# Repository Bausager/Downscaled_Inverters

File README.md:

# Downscaled three-phase half-bridge inverter
This project is an inverter framework for students and researches to learn, test and research state-of-the-art phase-lock-loops and control algorithms.
The inverters manly uses jellybean components, found free at the electronic laboratory for electrical engineers at Aarhus University(AU) for their students.
The purpose is to make an inexpensive and save platform instead of having to work with line voltages. 
This means all the components can be downscaled to work with 5 volt.
Here the inverter can be powered by a USB and supply its own grid.

This is an accumulative project, this means it's going to improve over time. 
There's a limited number of people working on this which means updates somethimes takes sometime.
If you want to help improve, collaborate or have something in your back pocket you want to integrate, you are very welcome to contact me!
The more the merrier!

There're some restrictions!
Since this is an open-source, student use it and research need to be understood and replicated, the code needs to be written in such a way that other prople can understand it.
Even if the person isn't an expert.
That is importent!

New fueatures waiting to be implemented can be found on the github project site [Not a Generator (NaG)](https://github.com/users/Bausager/projects/2)

## University Teaching

### Phase-Lock-Loop(PLL)
Many students at AU before this project have worked in PLLs for their bachelor thesis that meant a large part of the project was making an inverter from scratch.
This allows students not to reinvent the wheel if they are interested in other aspects than the hardware side.
With this the students can generate the grid and test their PLL on the some PCB, which lowest the bar of entre and in turn makes student projects and bachelor thesis more focused.

### Control
The students have the ability to develop control methods and test it only with a one inverter and output impedances.
Here different filter configuration or switching methods can also influence the THD which the students new have a direct way to interacting with.

### Power Factor Correction(PFC)
This PCB also allows to make it work as a PFC where control, THD and other aspects can be looked into.
Here a PFC input with a inverter output can also be pursued.

## Research Projects
Even if grid impedances does not downscale well, control algorithms, stability and many other advanced concept can be tested.
In the future, a new version of the PCB will be made for increasing the DC Link voltage to accommodate some of the downsides of the downscaled grid impedances.
As the time of writing the increase of DC Link voltage would be around 24V.
Now multiply inverters can be chained to a common grid to research stability.
Here the goal is not only to use the same micro-controller and control but to use different kinds of controls, PLLs, micro-controller, changing grid impedances, short-circuits and much more.
This will also include black start, synchronisation and much more.

## Collaborators
This project was initially an idea developed under [Associate Professor Uffe Jakobsen](https://pure.au.dk/portal/en/persons/uja%40ece.au.dk) for his classes and research into inverter control.
He also has students doing their project and bachelor thesis helping expand on this project.

A contributor [Christian Lind Vie Madsen](https://www.linkedin.com/in/christian-karl-oscar-lind-vie-madsen-11606a9b/) helps optimising written code for better performance.

And project maintainer- Me! [Michelle Bausager](https://www.linkedin.com/in/michelle-bausager/) A former student and research assistance at AU who likes to work with all aspects of inverters.

## Git Workflow.
For students or others who want to contribute, a workflow is needed to make sure everything still works in the end.
main.c on the main branch is written in such a way that every function is implementet but commented out.
This means there's a funtional implementation of every feature avaliable ready to use.

To make sure the workflow is allined a smal guide it here presented;

### Download the repository and work on an existing branch
Create of find a folder for the Git project and open your terminal in that folder.
Grab the git link and use the following git commands to download the project
```
git clone https://github.com/Bausager/Downscaled_Inverters.git
```
It’s good practice to get an overview of the project, especially the branches.
It's also here you would start if you come back to code some more!
```
git pull
git branch -a
```
There’s probably a need to code in a specific branch, if you're not in the right branch you need to select it from the list. 
Now you need to update it localy as follows:
```
git checkout specific_branch
git pull origin specific_branch
```
You can now start to make changes to the code!
To commit it, firstly you need to make sure the branch is up to date.
Then the "git add -A" commits all files and now you have to write some comments on the changes you made
Now you can push it to git!
```
git pull origin specific_branch
git add -A
git commit -m "Head line for changes
>
>
> Discription of what has been done "
git push origin specific_branch
```

### Make a new branch
Firstly make sure you have been invited to be a contributor.
Then starting working on a new feature first pull from the main branch
```
git pull origin main
```
Now you need to create a new branch where you can make your new implementations. Remember to give it a valuable name, such as "UltraCoolNewPLL".
After creating it you need to be in ýour new branch, with the opteration "checkout".
```
git branch new_branch
git checkout new_branch
```
You can now start to make changes to the code!
Since it's a new branch you don't need to make sure it's already updated as you do after you've commitet the branch for the first time.
Then the "git add -A" commits all files and now you have to write some comments on the changes you made.
```
git add -A
git commit -m "Head line for changes
>
>
> Discription of what has been done "
```
First time pushing a new branch you need to push it like this
```
git push -u origin new_branch
```
After that you can simply go to the workflow presented in *Download the repository and work on an existing branch*

### Marge branch to main
When the feature is done and tested, it's time to merge with the main branch.
This is the time and place where everything can go wrong!
Make sure main.c is steamlined like seen in the current main.c.
We're trying to implement every feature just outcommedted, that means you can just outcomment the feature to make it work.
At least that is what we're trying to do, to have a good example for the implementation for others to look at.
When we merge we need to be on the main branch.
```
git checkout main
git pull origin main
```
Now we can merge the branch into the main branch.
```
git merge new_branch
git push origin main
```
Now we’re ready to delete our branch. First we see what branches are merged, just to make sure we’re
deleting the right one. Then we delete the local branch and then the remote branch we associated with the
remote repository.
```
git branch --merged
git branch -d new_branch
git push origin --delete new_branch
```
And now it's done.

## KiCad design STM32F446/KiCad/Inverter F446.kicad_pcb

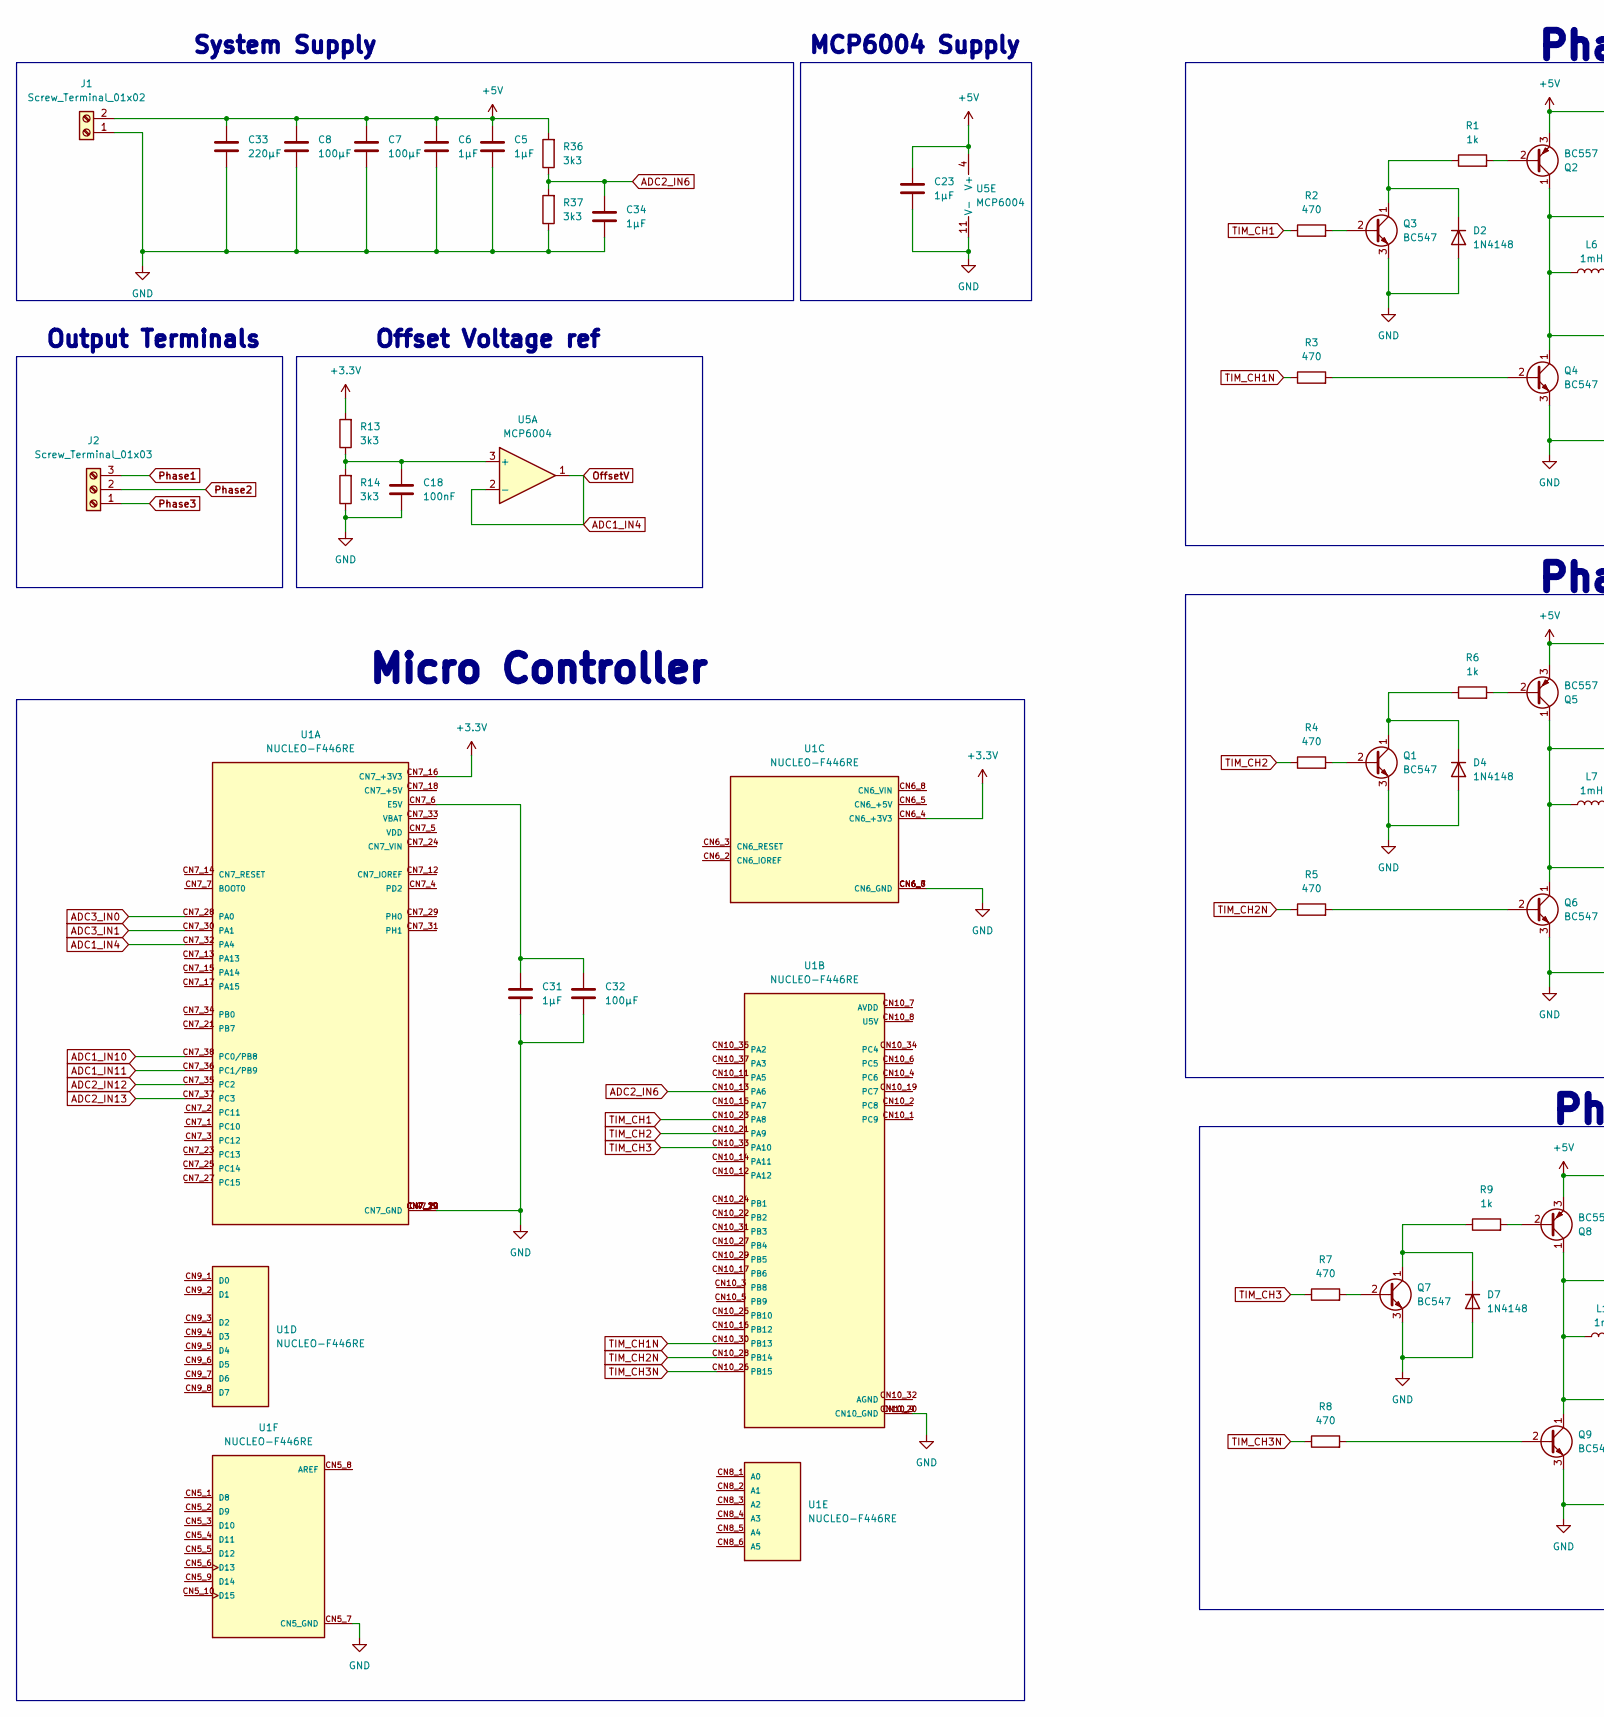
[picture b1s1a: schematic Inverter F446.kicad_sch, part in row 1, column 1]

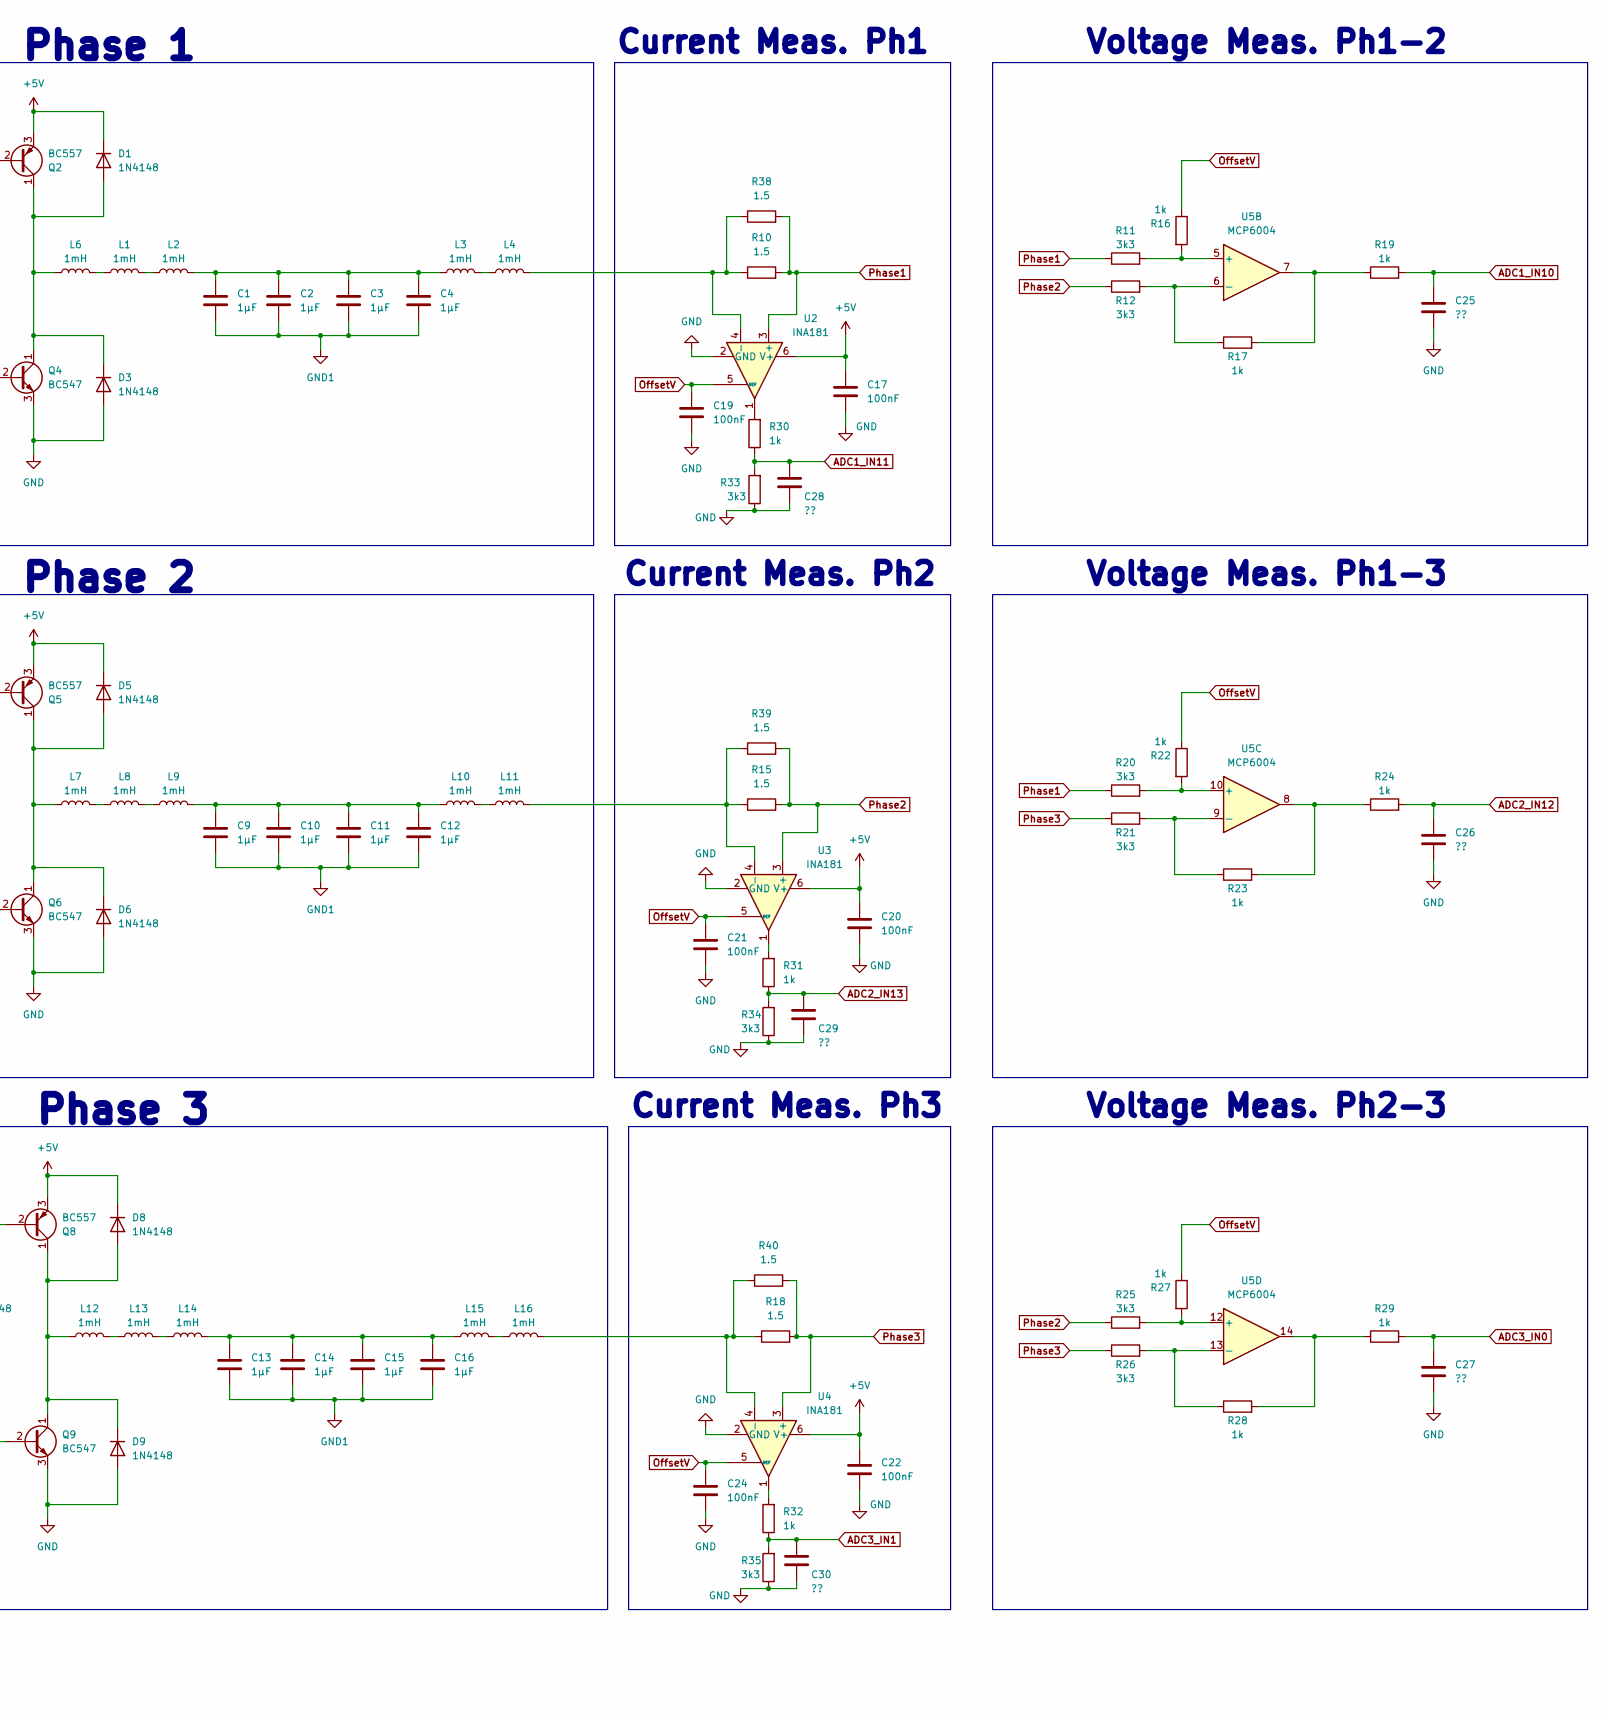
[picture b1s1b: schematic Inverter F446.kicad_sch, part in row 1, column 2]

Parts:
C1, C2, C3, C4, C5, C6, C9, C10, C11, C12, C13, C14, C15, C16, C23, C31, C34: 1µF; C_Disc_D7.5mm_W5.0mm_P5.00mm
C7, C8, C32: 100µF; CP_Radial_D6.3mm_P2.50mm
C17, C18, C19, C20, C21, C22, C24: 100nF; C_Disc_D7.5mm_W2.5mm_P5.00mm
C25, C26, C27, C28, C29, C30: ??; C_Disc_D7.5mm_W5.0mm_P5.00mm
C33: 220µF; CP_Radial_D8.0mm_P5.00mm
D1, D2, D3, D4, D5, D6, D7, D8, D9: 1N4148; D_DO-35_SOD27_P7.62mm_Horizontal
J1: Screw_Terminal_01x02; TerminalBlock_bornier-2_P5.08mm
J2: Screw_Terminal_01x03; TerminalBlock_bornier-3_P5.08mm
L1, L2, L3, L4, L6, L7, L8, L9, L10, L11, L12, L13, L14, L15, L16: 1mH; L_Axial_L12.0mm_D5.0mm_P15.24mm_Horizontal_Fastron_MISC
Q1, Q3, Q4, Q6, Q7, Q9: BC547; TO-92_Inline
Q2, Q5, Q8: BC557; TO-92_Inline
R1, R6, R9, R16, R17, R19, R22, R23, R24, R27, R28, R29, R30, R31, R32: 1k; R_Axial_DIN0207_L6.3mm_D2.5mm_P10.16mm_Horizontal
R2, R3, R4, R5, R7, R8: 470; R_Axial_DIN0207_L6.3mm_D2.5mm_P10.16mm_Horizontal
R10, R15, R18, R38, R39, R40: 1.5; R_Axial_DIN0207_L6.3mm_D2.5mm_P10.16mm_Horizontal
R11, R12, R13, R14, R20, R21, R25, R26, R33, R34, R35, R36, R37: 3k3; R_Axial_DIN0207_L6.3mm_D2.5mm_P10.16mm_Horizontal
U1: NUCLEO-F446RE; MODULE_NUCLEO-F446RE; PARTREV 13
U2, U3, U4: INA181; SOT-23-6
U5: MCP6004; DIP-14_W7.62mm_Socket

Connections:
+3.3V: R13.2, U1.CN6_4 (CN6_+3V3), U1.CN7_16 (CN7_+3V3)
+5V: C5.1, C6.1, C7.1, C8.1, C17.1, C20.1, C22.1, C23.1, C33.1, D1.1 (K), D5.1 (K), D8.1 (K), J1.2, Q2.3 (E), Q5.3 (E), Q8.3 (E), R36.2, U2.6 (V+), U3.6 (V+), U4.6 (V+), U5.4 (V+)
ADC1_IN4: C19.1, C21.1, C24.1, R16.1, R22.1, R27.1, U1.CN7_32 (PA4), U2.5 (REF), U3.5 (REF), U4.5 (REF), U5.1, U5.2 (-)
ADC1_IN10: C25.1, R19.2, U1.CN7_38 (PC0/PB8)
ADC1_IN11: C28.1, R30.1, R33.2, U1.CN7_36 (PC1/PB9)
ADC2_IN6: C34.1, R36.1, R37.2, U1.CN10_13 (PA6)
ADC2_IN12: C26.1, R24.2, U1.CN7_35 (PC2)
ADC2_IN13: C29.1, R31.1, R34.2, U1.CN7_37 (PC3)
ADC3_IN0: C27.1, R29.2, U1.CN7_28 (PA0)
ADC3_IN1: C30.1, R32.1, R35.2, U1.CN7_30 (PA1)
GND: C5.2, C6.2, C7.2, C8.2, C17.2, C18.2, C19.2, C20.2, C21.2, C22.2, C23.2, C24.2, C25.2, C26.2, C27.2, C28.2, C29.2, C30.2, C31.2, C32.2, C33.2, C34.2, D2.2 (A), D3.2 (A), D4.2 (A), D6.2 (A), D7.2 (A), D9.2 (A), J1.1, Q1.3 (E), Q3.3 (E), Q4.3 (E), Q6.3 (E), Q7.3 (E), Q9.3 (E), R14.1, R33.1, R34.1, R35.1, R37.1, U1.CN5_7 (CN5_GND), U1.CN6_6 (CN6_GND), U1.CN6_7 (CN6_GND), U1.CN7_8 (CN7_GND), U1.CN7_19 (CN7_GND), U1.CN7_20 (CN7_GND), U1.CN7_22 (CN7_GND), U1.CN10_9 (CN10_GND), U1.CN10_20 (CN10_GND), U2.2 (GND), U3.2 (GND), U4.2 (GND), U5.11 (V-)
GND1: C1.2, C2.2, C3.2, C4.2, C9.2, C10.2, C11.2, C12.2, C13.2, C14.2, C15.2, C16.2
unnamed: C1.1, C2.1, C3.1, C4.1, L2.2, L3.1
unnamed: C9.1, C10.1, C11.1, C12.1, L9.2, L10.1
unnamed: C13.1, C14.1, C15.1, C16.1, L14.2, L15.1
unnamed: D1.2 (A), D3.1 (K), L6.1, Q2.1 (C), Q4.1 (C)
unnamed: D2.1 (K), Q3.1 (C), R1.1
unnamed: D4.1 (K), Q1.1 (C), R6.1
unnamed: D5.2 (A), D6.1 (K), L7.1, Q5.1 (C), Q6.1 (C)
unnamed: D7.1 (K), Q7.1 (C), R9.1
unnamed: D8.2 (A), D9.1 (K), L12.1, Q8.1 (C), Q9.1 (C)
unnamed: L1.1, L6.2
unnamed: L1.2, L2.1
unnamed: L3.2, L4.1
unnamed: L7.2, L8.1
unnamed: L8.2, L9.1
unnamed: L10.2, L11.1
unnamed: L12.2, L13.1
unnamed: L13.2, L14.1
unnamed: L15.2, L16.1
unnamed: Q1.2 (B), R4.2
unnamed: Q2.2 (B), R1.2
unnamed: Q3.2 (B), R2.2
unnamed: Q4.2 (B), R3.2
unnamed: Q5.2 (B), R6.2
unnamed: Q6.2 (B), R5.2
unnamed: Q7.2 (B), R7.2
unnamed: Q8.2 (B), R9.2
unnamed: Q9.2 (B), R8.2
unnamed: R17.2, R19.1, U5.7
unnamed: R23.2, R24.1, U5.8
unnamed: R28.2, R29.1, U5.14
unnamed: R30.2, U2.1
unnamed: R31.2, U3.1
unnamed: R32.2, U4.1
unnamed: C31.1, C32.1, U1.CN7_6 (E5V)
unnamed: L4.2, R10.1, R38.1, U2.4 (-)
unnamed: L11.2, R15.1, R39.1, U3.4 (-)
unnamed: L16.2, R18.1, R40.1, U4.4 (-)
unnamed: C18.1, R13.1, R14.2, U5.3 (+)
unnamed: R11.2, R16.2, U5.5 (+)
unnamed: R12.2, R17.1, U5.6 (-)
unnamed: R20.2, R22.2, U5.10 (+)
unnamed: R21.2, R23.1, U5.9 (-)
unnamed: R25.2, R27.2, U5.12 (+)
unnamed: R26.2, R28.1, U5.13 (-)
Phase1: J2.3, R10.2, R11.1, R20.1, R38.2, U2.3 (+)
Phase2: J2.2, R12.1, R15.2, R25.1, R39.2, U3.3 (+)
Phase3: J2.1, R18.2, R21.1, R26.1, R40.2, U4.3 (+)
TIM_CH1: R2.1, U1.CN10_23 (PA8)
TIM_CH1N: R3.1, U1.CN10_30 (PB13)
TIM_CH2: R4.1, U1.CN10_21 (PA9)
TIM_CH2N: R5.1, U1.CN10_28 (PB14)
TIM_CH3: R7.1, U1.CN10_33 (PA10)
TIM_CH3N: R8.1, U1.CN10_26 (PB15)

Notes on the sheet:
Phase 1
Current Meas. Ph1
Current Meas. Ph3
System Supply
Micro Controller
Output Terminals
Voltage Meas. Ph1-3
Voltage Meas. Ph2-3
Offset Voltage ref
Voltage Meas. Ph1-2
Phase 2
Current Meas. Ph2
Phase 3
MCP6004 Supply

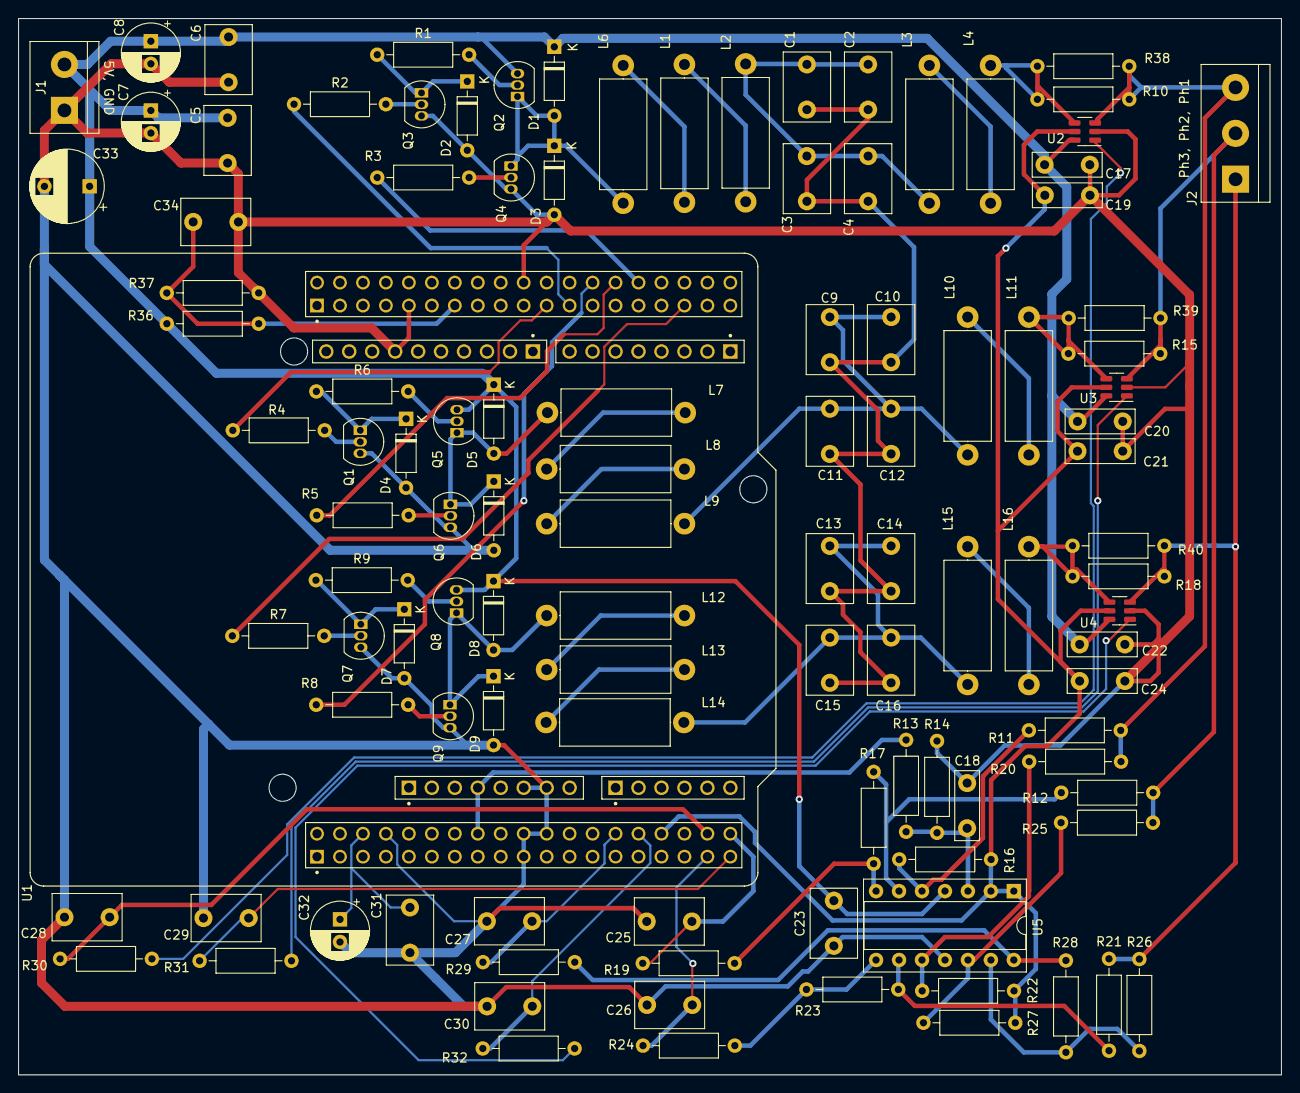
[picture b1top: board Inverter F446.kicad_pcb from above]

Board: 2 copper layers, 139.7 x 116.8 mm, 111 parts (0 on the bottom side), 65 nets.

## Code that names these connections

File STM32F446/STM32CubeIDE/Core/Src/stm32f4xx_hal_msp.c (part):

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    __HAL_RCC_GPIOC_CLK_ENABLE();
    __HAL_RCC_GPIOA_CLK_ENABLE();
    /**ADC1 GPIO Configuration
    PC0     ------> ADC1_IN10
    PC1     ------> ADC1_IN11
    PA4     ------> ADC1_IN4
    */
    GPIO_InitStruct.Pin = GPIO_PIN_0|GPIO_PIN_1;
    GPIO_InitStruct.Mode = GPIO_MODE_ANALOG;
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    __HAL_RCC_GPIOC_CLK_ENABLE();
    __HAL_RCC_GPIOA_CLK_ENABLE();
    /**ADC2 GPIO Configuration
    PC2     ------> ADC2_IN12
    PC3     ------> ADC2_IN13
    PA4     ------> ADC2_IN4
    PA6     ------> ADC2_IN6
    */
    GPIO_InitStruct.Pin = GPIO_PIN_2|GPIO_PIN_3;
    GPIO_InitStruct.Mode = GPIO_MODE_ANALOG;
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
    __HAL_RCC_GPIOA_CLK_ENABLE();
    /**ADC3 GPIO Configuration
    PA0-WKUP     ------> ADC3_IN0
    PA1     ------> ADC3_IN1
    */
    GPIO_InitStruct.Pin = GPIO_PIN_0|GPIO_PIN_1;
    GPIO_InitStruct.Mode = GPIO_MODE_ANALOG;
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    __HAL_RCC_ADC1_CLK_DISABLE();

    /**ADC1 GPIO Configuration
    PC0     ------> ADC1_IN10
    PC1     ------> ADC1_IN11
    PA4     ------> ADC1_IN4
    */
    HAL_GPIO_DeInit(GPIOC, GPIO_PIN_0|GPIO_PIN_1);

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    __HAL_RCC_ADC2_CLK_DISABLE();

    /**ADC2 GPIO Configuration
    PC2     ------> ADC2_IN12
    PC3     ------> ADC2_IN13
    PA4     ------> ADC2_IN4
    PA6     ------> ADC2_IN6
    */
    HAL_GPIO_DeInit(GPIOC, GPIO_PIN_2|GPIO_PIN_3);

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    __HAL_RCC_ADC3_CLK_DISABLE();

    /**ADC3 GPIO Configuration
    PA0-WKUP     ------> ADC3_IN0
    PA1     ------> ADC3_IN1
    */
    HAL_GPIO_DeInit(GPIOA, GPIO_PIN_0|GPIO_PIN_1);

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    __HAL_RCC_GPIOB_CLK_ENABLE();
    __HAL_RCC_GPIOA_CLK_ENABLE();
    /**TIM1 GPIO Configuration
    PB13     ------> TIM1_CH1N
    PB14     ------> TIM1_CH2N
    PB15     ------> TIM1_CH3N
    PA8     ------> TIM1_CH1
    PA9     ------> TIM1_CH2
    PA10     ------> TIM1_CH3
    */
    GPIO_InitStruct.Pin = GPIO_PIN_13|GPIO_PIN_14|GPIO_PIN_15;
    GPIO_InitStruct.Mode = GPIO_MODE_AF_PP;
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
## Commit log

2023-12-25 Initial Work
2023-12-30 PWM and ADC tested
2023-12-30 A bit of clean up
2024-01-01 Folder cleanup
2024-01-01 PCB makeing
2024-01-02 PCB Placement Done
2024-01-03 A bit of clean-up
2024-01-03 Deleting zip-files
2024-01-03 Uploadning for homwork
2024-01-04 First Routing
2024-01-04 Generated Gaber files
2024-02-12 ADCmeas.c/h created
2024-02-13 Starting meas files
2024-02-14 Starting on meas.Calc
2024-02-15 just starting to make optimizations..
2024-02-15 Intantaniu Power calculation is done.
2024-02-16 RMS calculations seems to work
2024-02-16 RMS calc clean-up
2024-02-16 Clean-up
2024-02-17 starting on DQ Tranformation and PLL
2024-02-17 dqPLL works
2024-02-17 dqPLL test It's somtimes 180 degrees off, sometimes spot on. Don't know why yet
2024-02-18 Grid Estimator doesn't work yet
2024-02-19 Grid Estimation Work
2024-02-20 dqPLL works :)
2024-02-20 .png to gitignore
2024-02-21 Cleanup
2024-02-21 Comments, test case in main and cleanup
2024-02-22 Something is wrong with the power calculations and measurement calc
2024-02-23 Q Calculations works
2024-02-23 Updating transfCalc
    I've updated transfCalc to use constants instead of defining everything. Tested and works
    dqPLL still either hugs 0.01 or 3.14 rad from the target and don't know why, yet!
    Cleaning up code is next
2024-02-24 Cleanup and Commenting
    All is more or less clean up with comments and referances to used material, articles and pattens.
2024-02-24 Update README.md
    Update README. Still missing pictures
2024-02-24 Update README.md
    Updated with link to project
2024-02-25 Const for input variables
    Fixed so every input for functions are const, every output is ether a pointer or a return.
    This makes it esaier to see what is the function input and outputs
2024-02-25 LCL Phase compensation is done
    LCL phaseshift is calculated and integrated into dqPLL for angle compensation
    Since I'm an idiot i've also fixed some of the problems with the dqPLL.
    Now the PI coeff are calculated correctly
    I used the grid frequency before. I now use the angular grid frequency and it seems more stable
    #SundayWork
2024-02-26 AlphaBetaPLL and more
    I've gotten the AlphaBetaPLL to work. But there's still something about the LCL anlge compensaton.
2024-02-26 fixed angle compensation
2024-02-27 Update README.md
    Updated for git workflow
2024-02-28 Fixed minor error in SVM block
2024-03-03 Droop Control on Resistive grid (formning)
    Not commented yet but works
2024-03-10 Fixed Ud_to_Mi

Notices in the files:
STM32F446/STM32CubeIDE/Core/Src/stm32f4xx_hal_msp.c:
Copyright (c) 2023 STMicroelectronics.
All rights reserved.
This software is licensed under terms that can be found in the LICENSE file
